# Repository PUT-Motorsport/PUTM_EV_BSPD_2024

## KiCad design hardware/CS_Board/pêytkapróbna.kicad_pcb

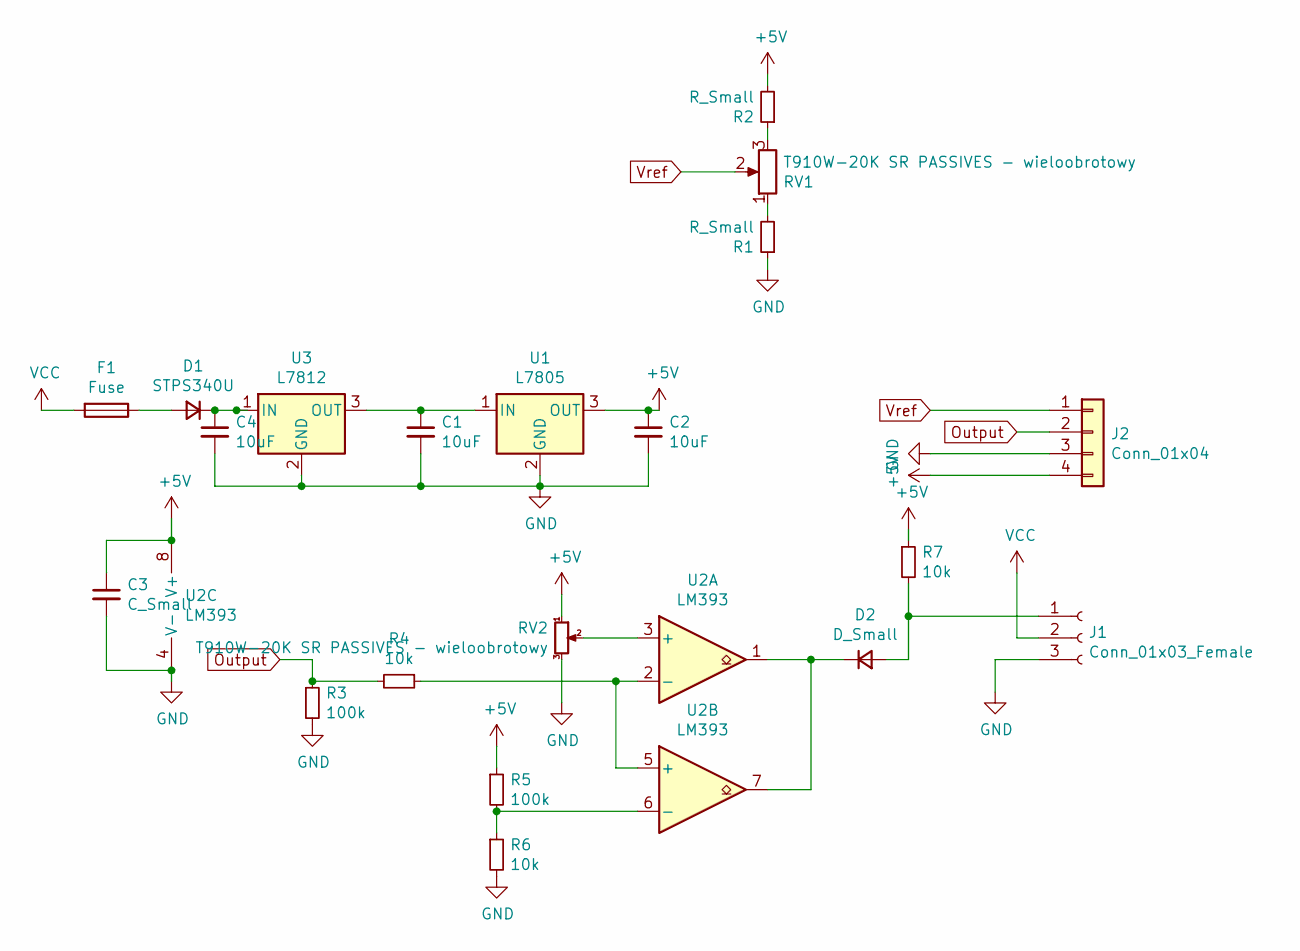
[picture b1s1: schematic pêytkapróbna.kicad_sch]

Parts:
C1, C2, C4: 10uF; C_1206_3216Metric
C3: C_Small; C_1206_3216Metric
D1: STPS340U; D_SMB
D2: D_Small; D_SMB
F1: Fuse; D_SMB
J1: Conn_01x03_Female; 436500304
J2: Conn_01x04; current_sensor
R1, R2: R_Small; D_1206_3216Metric
R3, R5: 100k; R_1206_3216Metric
R4, R6, R7: 10k; R_1206_3216Metric
RV1, RV2: T910W-20K SR PASSIVES - wieloobrotowy; Potentiometer_Bourns_3296W_Vertical
U1: L7805; TO-252-3_TabPin2
U2: LM393; PowerIntegrations_SO-8
U3: L7812; TO-252-3_TabPin2

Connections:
+5V: C2.1, C3.1, J2.4, R2.2, R5.1, R7.1, RV2.1, U1.3 (OUT), U2.8 (V+)
GND: C1.2, C2.2, C3.2, C4.2, J1.3, J2.3, R1.1, R3.2, R6.2, RV2.3, U1.2 (GND), U2.4 (V-), U3.2 (GND)
unnamed: D1.2 (A), F1.1
unnamed: C4.1, D1.1 (K), U3.1 (IN)
unnamed: D2.2 (A), J1.1, R7.2
unnamed: D2.1 (K), U2.1, U2.7
unnamed: R1.2, RV1.1
unnamed: R2.1, RV1.3
unnamed: C1.1, U1.1 (IN), U3.3 (OUT)
unnamed: RV2.2, U2.3 (+)
unnamed: R4.1, U2.2 (-), U2.5 (+)
unnamed: R5.2, R6.1, U2.6 (-)
Output: J2.2, R3.1, R4.2
VCC: F1.2, J1.2
Vref: J2.1, RV1.2

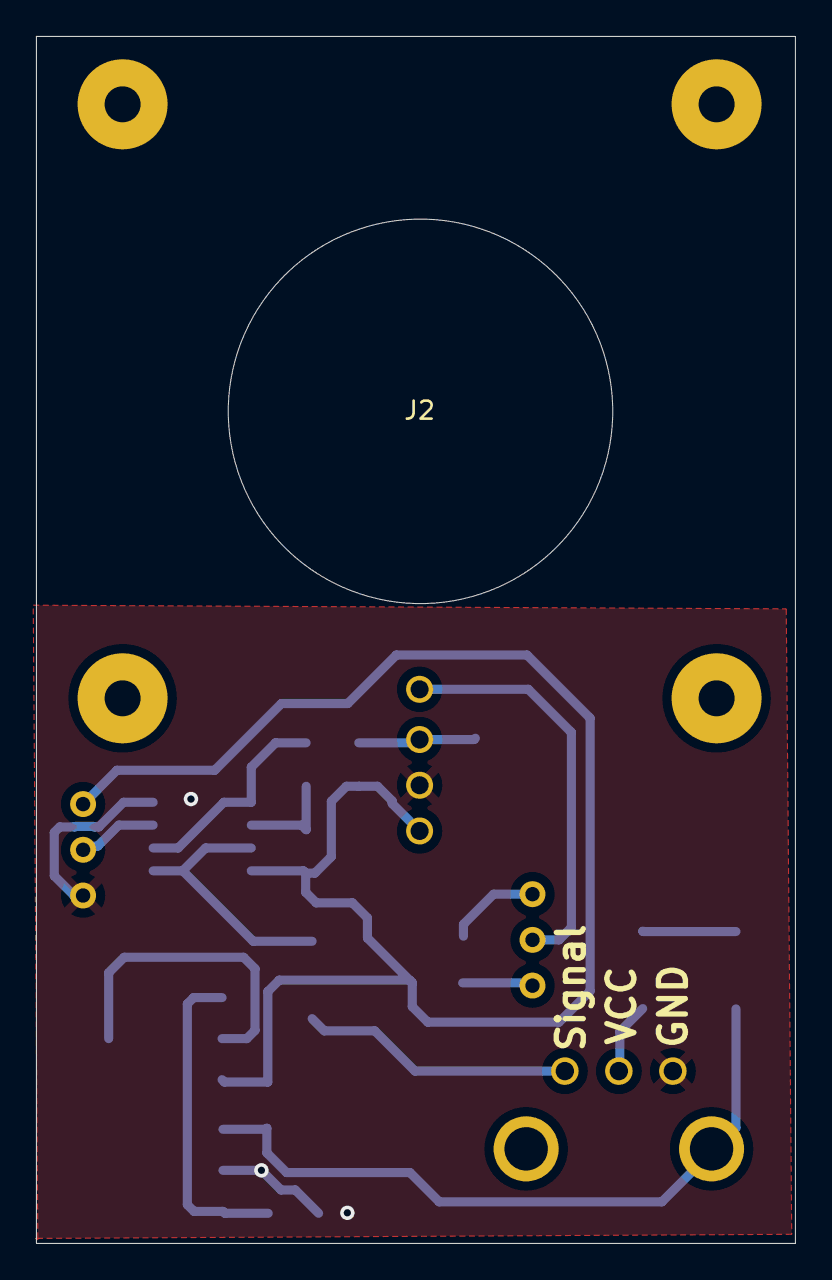
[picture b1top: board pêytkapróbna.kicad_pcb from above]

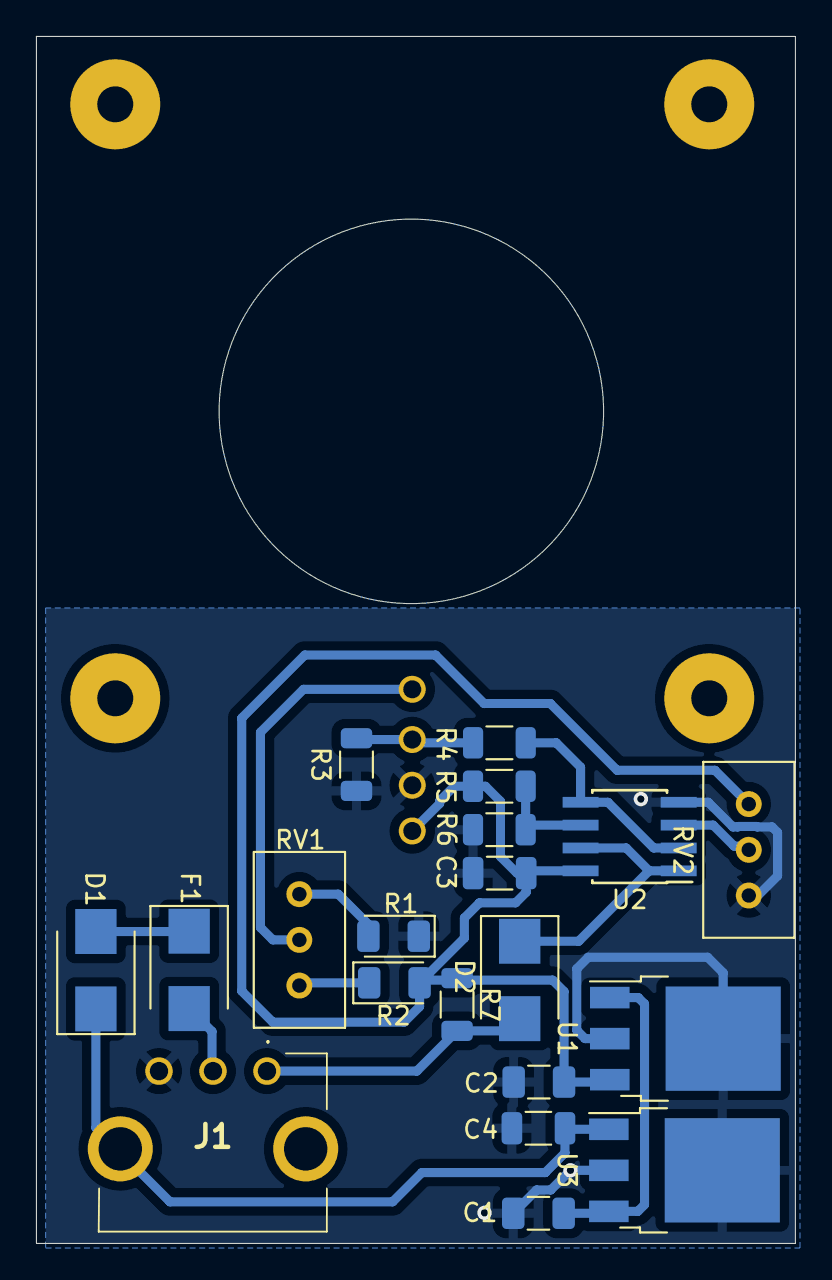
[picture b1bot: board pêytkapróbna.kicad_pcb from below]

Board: 2 copper layers, 42.2 x 67.1 mm, 21 parts (20 on the bottom side), 15 nets.

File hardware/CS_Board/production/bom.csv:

Designator,Footprint,Quantity,Value,LCSC Part #
"C1, C2, C4",1206,3,10uF,
C3,1206,1,C_Small,
D1,D_SMB,1,STPS340U,
D2,D_SMB,1,D_Small,
F1,D_SMB,1,Fuse,
J1,436500304,1,Conn_01x03_Female,
J2,current_sensor,1,Conn_01x04,
"R1, R2",1206,2,R_Small,
"R3, R5",1206,2,100k,
"R4, R6, R7",1206,3,10k,
"RV1, RV2",Potentiometer_Bourns_3296W_Vertical,2,T910W-20K SR PASSIVES - wieloobrotowy,
U1,TO-252-3_TabPin2,1,L7805,
U2,PowerIntegrations_SO-8,1,LM393,
U3,TO-252-3_TabPin2,1,L7812,

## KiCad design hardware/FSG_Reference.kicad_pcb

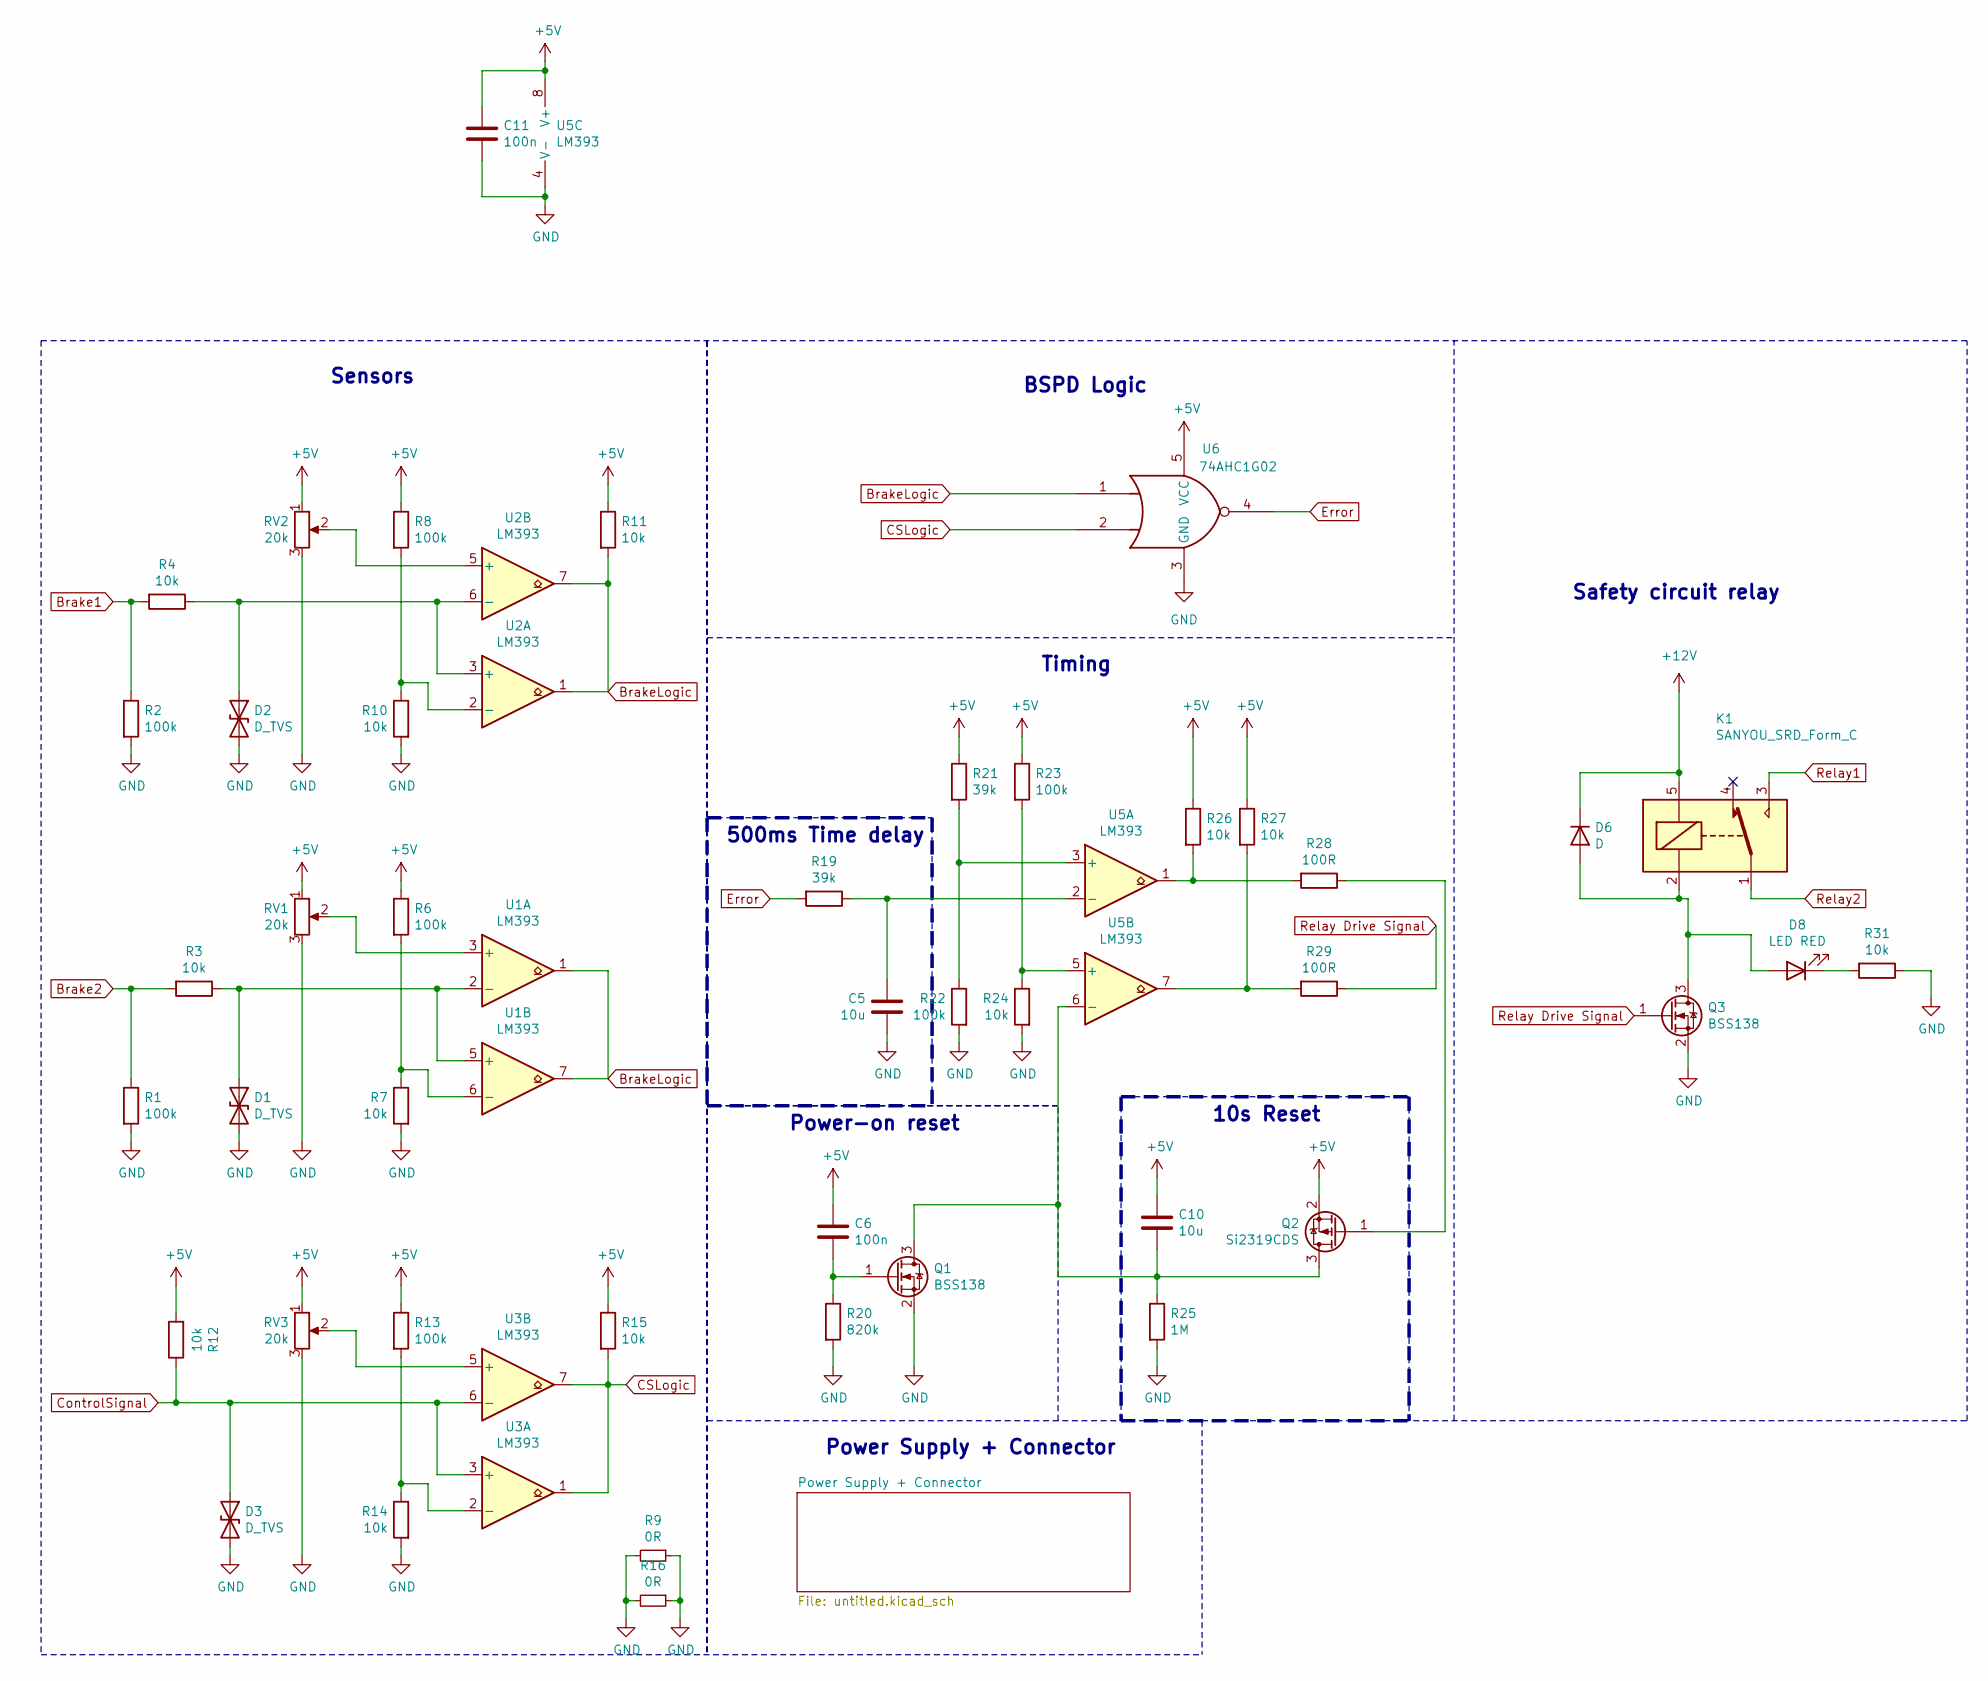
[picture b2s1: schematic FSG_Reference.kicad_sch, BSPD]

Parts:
C5, C10: 10u; C_1206_3216Metric
C6, C11: 100n; C_1206_3216Metric
D1, D2, D3: D_TVS; D_SMB
D6: D; D_SMB
D8: LED RED; LED_PLCC-2
K1: SANYOU_SRD_Form_C; Relay_SPDT_SANYOU_SRD_Series_Form_C
Q1, Q3: BSS138; SOT-23
Q2: Si2319CDS; SOT-23
R1, R2, R6, R8, R13, R22, R23: 100k; R_1206_3216Metric
R3, R4, R7, R10, R11, R12, R14, R15, R24, R26, R27, R31: 10k; R_1206_3216Metric
R9, R16: 0R; R_1206_3216Metric
R19, R21: 39k; R_1206_3216Metric
R20: 820k; R_1206_3216Metric
R25: 1M; R_1206_3216Metric
R28, R29: 100R; R_1206_3216Metric
RV1, RV2, RV3: 20k; Potentiometer_ACP_CA9-H2,5_Horizontal
U1, U2, U3, U5: LM393; SOIC-8_3.9x4.9mm_P1.27mm
U6: 74AHC1G02; SOT-353_SC-70-5

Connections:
+5V: C6.1, C10.1, C11.1, Q2.2 (S), R6.1, R8.1, R11.1, R12.2, R13.1, R15.1, R21.1, R23.1, R26.1, R27.1, RV1.1, RV2.1, RV3.1, U5.8 (V+), U6.5 (VCC); also elsewhere on the board
+12V: D6.1 (K), K1.5; also elsewhere on the board
Brake1: R2.1, R4.2; also elsewhere on the board
Brake2: R1.1, R3.2; also elsewhere on the board
BrakeLogic: R11.2, U1.1, U1.7, U2.1, U2.7, U6.1
CSLogic: R15.2, U3.1, U3.7, U6.2
ControlSignal: D3.1 (A1), R12.1, U3.3 (+), U3.6 (-); also elsewhere on the board
Error: R19.2, U6.4
GND: C5.2, C11.2, D1.2 (A2), D2.2 (A2), D3.2 (A2), Q1.2 (S), Q3.2 (S), R1.2, R2.2, R7.2, R9.1, R9.2, R10.2, R14.2, R16.1, R16.2, R20.2, R22.2, R24.2, R25.2, R31.1, RV1.3, RV2.3, RV3.3, U5.4 (V-), U6.3 (GND); also elsewhere on the board
unnamed: D1.1 (A1), R3.1, U1.2 (-), U1.5 (+)
unnamed: D2.1 (A1), R4.1, U2.3 (+), U2.6 (-)
unnamed: D6.2 (A), D8.2 (A), K1.2, Q3.3 (D)
unnamed: D8.1 (K), R31.2
unnamed: C10.2, Q1.3 (D), Q2.3 (D), R25.1, U5.6 (-)
unnamed: C6.2, Q1.1 (G), R20.1
unnamed: Q2.1 (G), R28.1
unnamed: R26.2, R28.2, U5.1
unnamed: R27.2, R29.2, U5.7
unnamed: RV1.2, U1.3 (+)
unnamed: R6.2, R7.1, U1.6 (-)
unnamed: R8.2, R10.1, U2.2 (-)
unnamed: RV2.2, U2.5 (+)
unnamed: R13.2, R14.1, U3.2 (-)
unnamed: RV3.2, U3.5 (+)
unnamed: R21.2, R22.1, U5.3 (+)
unnamed: C5.1, R19.1, U5.2 (-)
unnamed: R23.2, R24.1, U5.5 (+)
Relay1: K1.3; also elsewhere on the board
Relay2: K1.1; also elsewhere on the board
Relay Drive Signal: Q3.1 (G), R29.1

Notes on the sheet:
Power-on reset
Sensors
Safety circuit relay
Power Supply + Connector
BSPD Logic
10s Reset
500ms Time delay
Timing

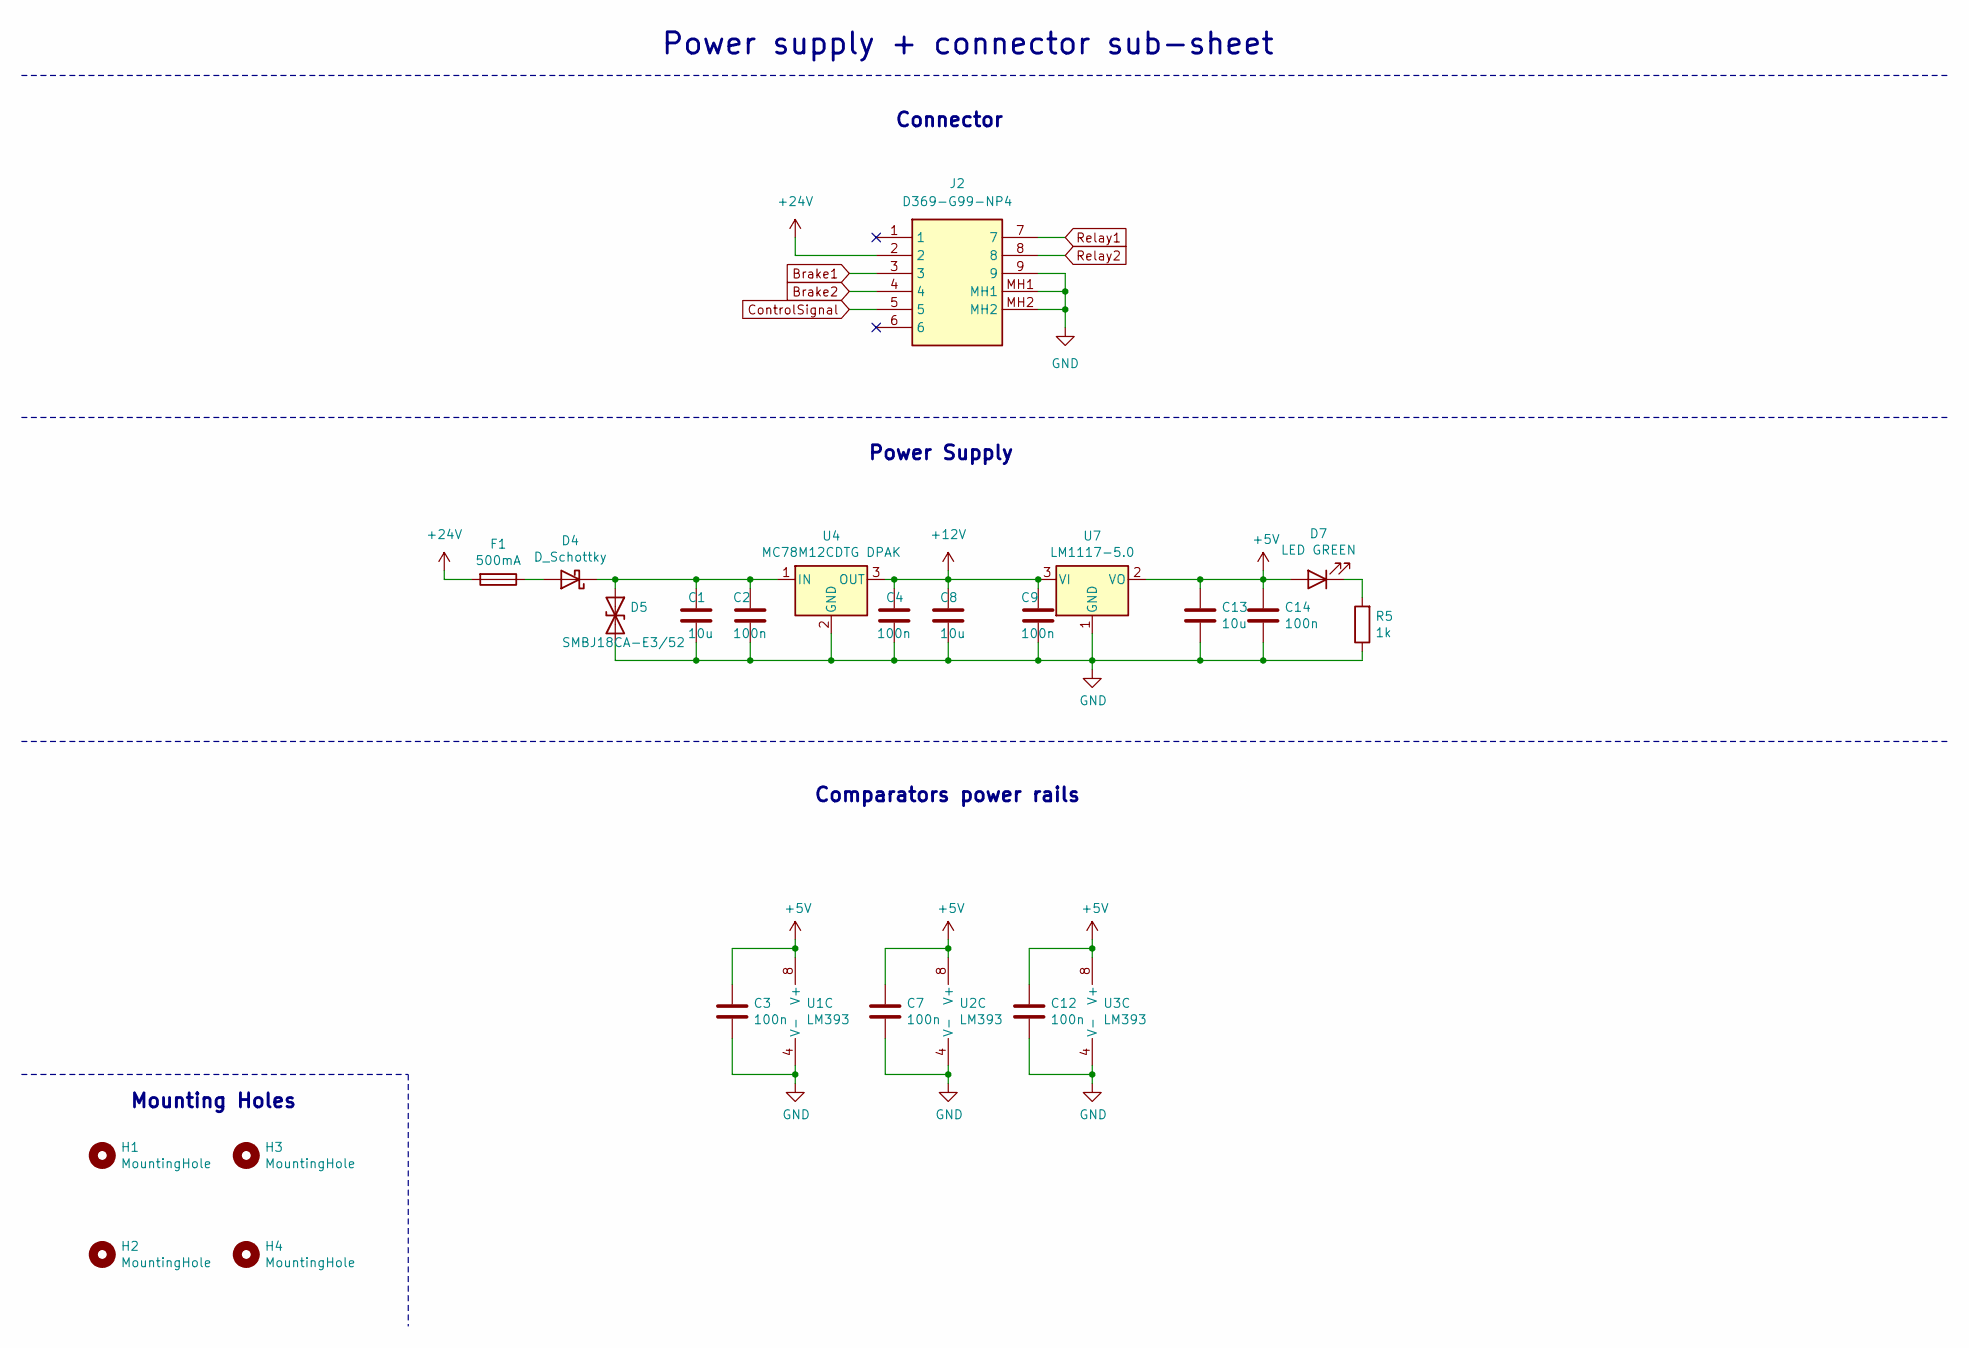
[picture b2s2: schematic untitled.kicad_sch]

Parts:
C1, C8, C13: 10u; C_1206_3216Metric
C2, C3, C4, C7, C9, C12, C14: 100n; C_1206_3216Metric
D4: D_Schottky; D_SMB
D5: SMBJ18CA-E3/52; D_SMB
D7: LED GREEN; LED_PLCC-2
F1: 500mA; Fuse_1206_3216Metric
H1, H2, H3, H4: MountingHole; MountingHole_3.2mm_M3_ISO7380
J2: D369-G99-NP4; D369G99NP4; Mouser Part Number 571-D369-G99-NP4
R5: 1k; R_1206_3216Metric
U1, U2, U3: LM393; SOIC-8_3.9x4.9mm_P1.27mm
U4: MC78M12CDTG DPAK; TO-252-3_TabPin2
U7: LM1117-5.0; SOT-223

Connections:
+5V: C3.1, C7.1, C12.1, C13.1, C14.1, D7.2 (A), U1.8 (V+), U2.8 (V+), U3.8 (V+), U7.2 (VO); also elsewhere on the board
+12V: C4.1, C8.1, C9.1, U4.3 (OUT), U7.3 (VI); also elsewhere on the board
+24V: F1.2, J2.2
Brake1: J2.3; also elsewhere on the board
Brake2: J2.4; also elsewhere on the board
ControlSignal: J2.5; also elsewhere on the board
GND: C1.2, C2.2, C3.2, C4.2, C7.2, C8.2, C9.2, C12.2, C13.2, C14.2, D5.2 (A2), J2.9, J2.MH1, J2.MH2, R5.1, U1.4 (V-), U2.4 (V-), U3.4 (V-), U4.2 (GND), U7.1 (GND); also elsewhere on the board
unnamed: D4.2 (A), F1.1
unnamed: C1.1, C2.1, D4.1 (K), D5.1 (A1), U4.1 (IN)
unnamed: D7.1 (K), R5.2
Relay1: J2.7; also elsewhere on the board
Relay2: J2.8; also elsewhere on the board

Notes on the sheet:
Connector
Mounting Holes
Power Supply
Power supply + connector sub-sheet
Comparators power rails

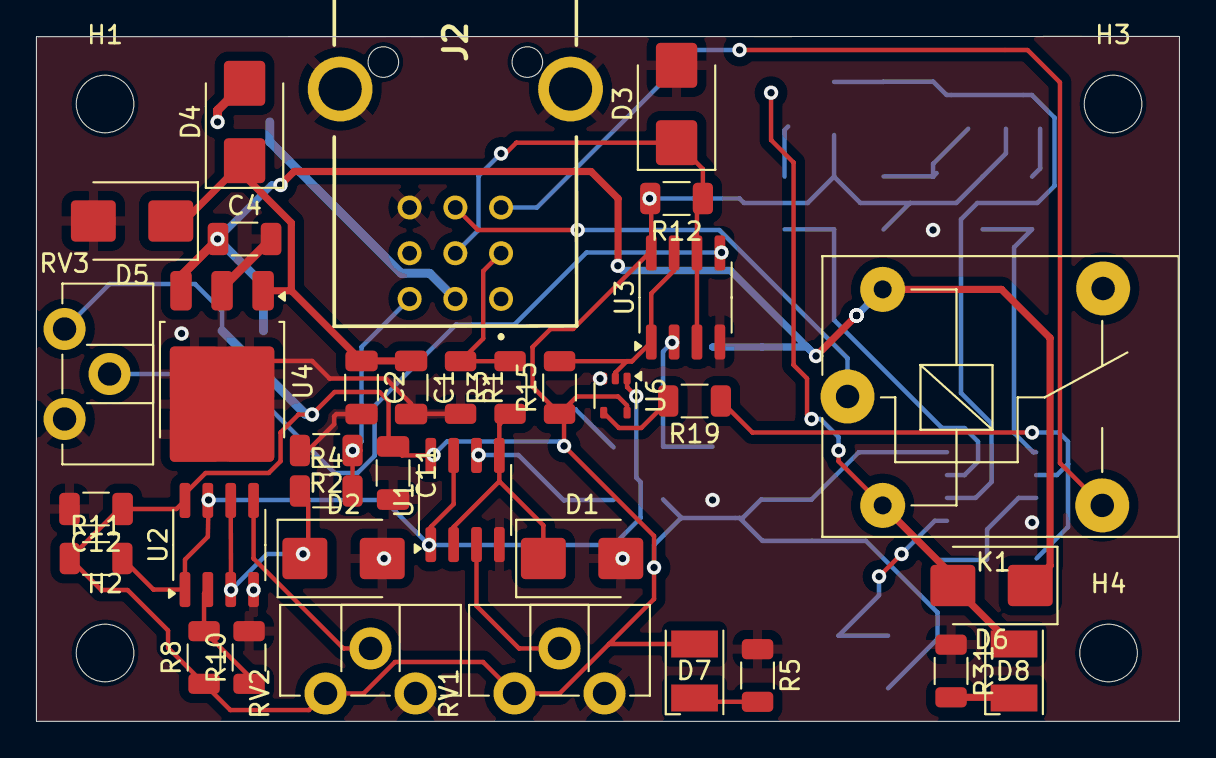
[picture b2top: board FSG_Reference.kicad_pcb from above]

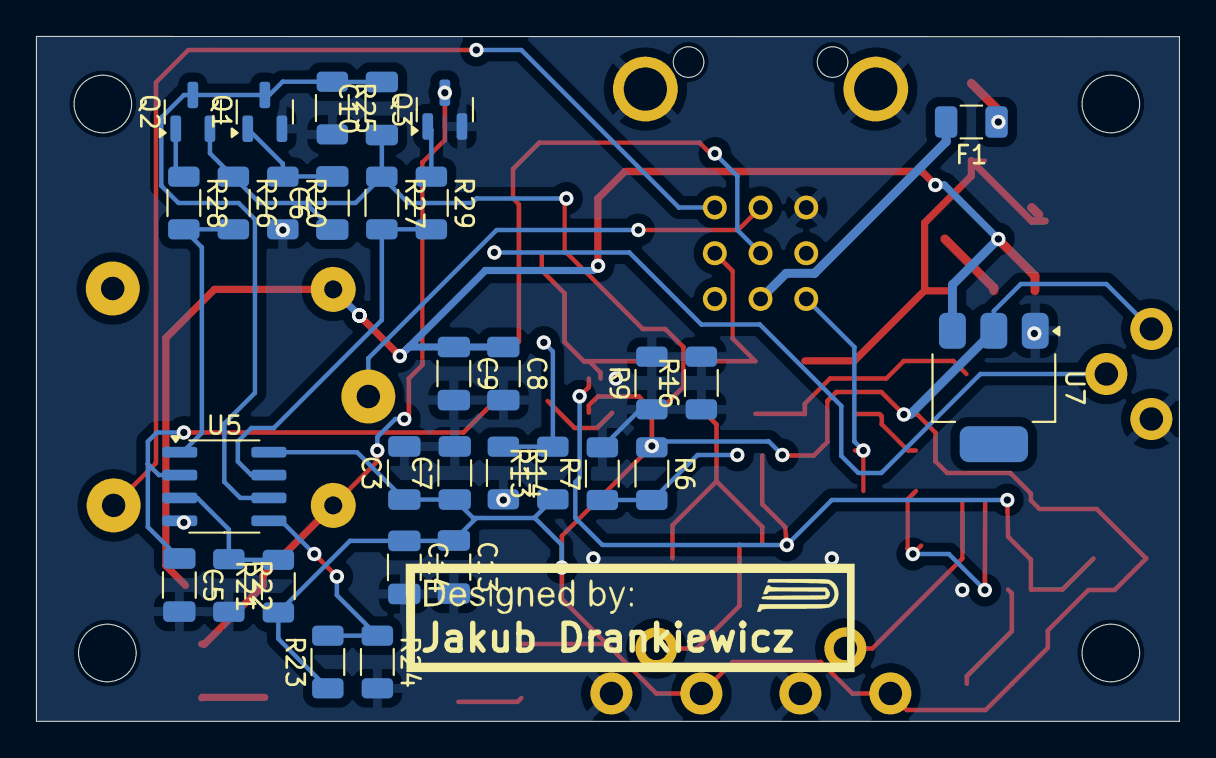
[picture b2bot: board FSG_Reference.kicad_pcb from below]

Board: 4 copper layers, 63.5 x 38.0 mm, 70 parts (31 on the bottom side), 34 nets.

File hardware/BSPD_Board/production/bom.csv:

Designator,Footprint,Quantity,Value,LCSC Part #
"C1, C11, C13, C15, C2, C3, C6, C7, C9",1206,9,100n,
"C10, C12, C4, C5, C8",1206,5,10u,
"D1, D2, D3",D_SMB,3,D_TVS,
D4,D_SMB,1,D_Schottky,
D5,D_SMB,1,SMBJ18CA-E3/52,
D6,D_SMB,1,D,
D7,1206,1,LED GREEN,
D8,1206,1,LED RED,
F1,1206,1,500mA,
"H1, H2, H3",MountingHole_3.2mm_M3_ISO7380,3,MountingHole,
J2,D369G99NP4,1,D369-G99-NP4,
K1,Relay_SPDT_SANYOU_SRD_Series_Form_C,1,SANYOU_SRD_Form_C,
"Q1, Q3",SOT-23,2,BSS138,
Q2,SOT-23,1,Si2319CDS,
"R1, R10, R22, R23, R4, R7",1206,6,100k,
"R11, R12, R13, R24, R26, R27, R3, R31, R6, R8",1206,10,10k,
"R19, R21",1206,2,39k,
R20,1206,1,820k,
R25,1206,1,1M,
"R28, R29",1206,2,100R,
R30,1206,1,1k,
"RV1, RV2","Potentiometer_ACP_CA9-H2,5_Horizontal",2,20k,
"U1, U2, U5",SOIC-8_3.9x4.9mm_P1.27mm,3,LM393,
U4,SOT-223,1,LM1117-5.0,
U6,SOT-23-5,1,74AHC1G02,
U7,TO-252-3_TabPin2,1,MC78M12CDTG DPAK,

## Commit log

2024-03-19 changed the whole layout
2024-03-19 Added production
2024-03-19 added options
2024-04-22 Changed the connector
2024-04-23 fixed connections
2024-04-24 fixed the error of the connector, now 0 errors
2024-10-10 New BSPD Layout based on BSPD by Jakub Drankiewicz in 2021
    -Schematic needs to be adjusted for better understanding
    -Comparator of Current Sensor removed, the one on Current Sensor Board is sufficient
2024-10-10 Current Sensor Board added and BSPD board moved
    -Hardware volume architecture changed with both boards on repo
